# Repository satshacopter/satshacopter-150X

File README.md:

<h1 style="font-family: courier;" align="center">satshacopter 150X</h1>
<p align="center">

<div align="center"><i>An open source,small, low cost and fabbable quad X drone.</i></div>
</p>  

satshacopter 150X
--

satshacopter 150X is a quadcopter built around the **[satshakit mini flight controller](https://github.com/satshakit/satshakit-mini-flight-controller)** and derived from its big brother **[satshacopter 250X](https://github.com/satshacopter/satshacopter-250X)**. It is designed to be **simple and cheap as much as possible**, and to be easily made inside any **Fab Lab**.

150X specifications:

- **150mm mdf frame** and supports
- **open source flight controller**
- **MPU6050 IMU** located exactly at the center
- 4 x 3100kv **brushless motors**
- 4 x 6A **ESCs**
- **MultiWii** compatible
- Hobby King 4 channel **remote and receiver**
- 1000mah 2S 65C **LiPo battery** 
- costs around **100€**

Here you can look about the **MultiWii pin mapping** of the satshakit mini flight controller board:

And here you can che the required components in the **Bill of Material** table:

|name|description|vendor|link|price|notes|
|:---:| :---:|:---:|:---:|:---:|:---:|
|2.4Ghz4Ch TxRx V2|4ch mode 2 remote control and receiver|Hobby King|[link](http://www.hobbyking.com/hobbyking/store/__66499__Hobby_King_2_4Ghz_4Ch_Tx_Rx_V2_Mode_2_EU_Warehouse_.html)|23.14€|-|
|Turnigy Graphene|battery 1000mah 2s 65C|Hobby King|[link](https://hobbyking.com/en_us/graphene-1000mah-2s-65c-w-xt60.html)|8.42€|-|
|LDPOWER D150 Multicopter Power System|4 x MT1306-3100KV motors and 4 x 6A esc|Hobby King EU|[link](https://hobbyking.com/en_us/ldpower-d150-multicopter-power-system-mt1306-3100kv-4-x-4-5-4-pack.html)|59.26€|propellers Included|
|IMU 6DOF|MPU6050 Gyro + Acc IMU|Ebay|[link](http://www.ebay.de/itm/MPU-6050-GY-521-3-Achsen-Gyroskop-Accelerometer-Kreisel-Board-Sensor-Arduino-21-/121887579651)|5.39€|-|
|LiPo Charger and Balancer|800mah 3s LiPo charger|Hobby King|[link](http://www.hobbyking.com/hobbyking/store/uh_viewitem.asp?idproduct=77525)|6.99€|-|
|Fligh Controller|satshakit mini flight controller|various|[link](https://github.com/satshakit/satshakit-flight-controller)|4.00-8.00€|depending on the quantity|
||||**Total price**|103.2€+4/8€|-|

NOTE: prices may change over time on the respective vendors, and also it is highly dependand on the quantity of drones you want to make.

Downloads
--

If you want to build by yourself a satshacopter 150X, please download the detailed **satshacopter 250X build manual** as a reference guide:

- [satshacopter 250X detailed build manual](https://github.com/satshacopter/satshacopter-250X/raw/master/docs/250X/satshacopter-250x-building-manual.pdf)

Following you can find all the **design files** you need to make it:

- [satshakit mini flight controller eagle board](https://github.com/satshacopter/satshacopter-150X/raw/master/eagle_projects/satshakit_mini_flight_controller/satshakit_mini_fc.brd)
- [satshakit mini flight controller eagle sch](https://github.com/satshacopter/satshacopter-150X/raw/master/eagle_projects/satshakit_mini_flight_controller/satshakit_mini_fc.sch)
- [satshakit mini flight controller internal traces png](https://github.com/satshacopter/satshacopter-150X/raw/master/media/satshakit_mini_fc_internal.png)
- [satshakit flight controller cut png](https://github.com/satshacopter/satshacopter-150X/raw/master/media/satshakit_mini_fc_cut.png)
- [mini frame and supports Rhino](https://github.com/satshacopter/satshacopter-150X/raw/master/design_files/frame_and_supports_3mm.3dm)
- [mini frame dxf](https://github.com/satshacopter/satshacopter-150X/raw/master/design_files/frame.dxf)
- [mini supports dxf](https://github.com/satshacopter/satshacopter-150X/raw/master/design_files/supports.dxf)
- [mini foot Rhino](https://github.com/satshacopter/satshacopter-150X/raw/master/design_files/foot.3dm)
- [mini foot STL](https://github.com/satshacopter/satshacopter-150X/raw/master/design_files/foot.stl)

Media
--

Some images of a satshacopter 150X:

Safety
--

Please try always to fly safe.

Here are my personal safety recommendations, especially for experimental drones of which you are not sure on how they can behave:

- make sure to always keep an HUGE distance between you and the drone
- always place yourself on the back of the drone before starting flying
- always have the direct sight to the drone and make sure that its orientation is clear for you (use different colors or LEDs)
- fly in private areas where no public can access
- make sure that nobody can come near the drone while you are flying
- make sure that you cannot destroy anything that you have around you with the drone
- check the wind and the weather before flying, if outdoor
- never go too high (no more than 1/2 meters in these cases)
- do not fly on top of someone (neither yourself)
- first try to fly few cm above the ground to see if everything is correct
- try to avoid using carbon fiber props (they are really like rotating knifes) but use plastic props
- try to use smaller drones with smaller props for really experimental tests
- triple check all the screws and that the frame is not cracked somewhere
- triple check all the DIY electronics, if it fails in-flight can be extremely dangerous
- make sure that the batteries are full charged (both transmitter and the LiPos)

Authors
--

- Daniele Ingrassia

Contact
--

- **ingrassiada@gmail.com**
- **[linkedin](http://it.linkedin.com/in/danieleingrassia)**

Thanks
--

Aldo Sollazzo<br />
[Noumena](http://noumena.io/)<br />
Carrer de Pere IV 29-35, 4-1, Poblenou, 08018, Barcelona, Spain<br />
t: (+34) 652964886<br />
aldo@noumena.io <br />

[Fablab Kamp-Lintfort](http://fablab.hochschule-rhein-waal.de/index.php/de/)<br />
Hochschule Rhein-Waal<br />
Friedrich-Heinrich-Allee 25, 47475 Kamp-Lintfort, Germany<br />
fablab@hochschule-rhein-waal.de

License
--

This work is licensed under the terms of the open source license: Creative Commons Attribution-ShareAlike 4.0 International ([CC BY-SA 4.0](https://creativecommons.org/licenses/by-sa/4.0/)).

Disclaimer  
--

<div class="align-justify">
This hardware/software is provided "as is", and you use the hardware/software at your own risk. Under no circumstances shall any author be liable for direct, indirect, special, incidental, or consequential damages resulting from the use, misuse, or inability to use this hardware/software, even if the authors have been advised of the possibility of such damages.</div>

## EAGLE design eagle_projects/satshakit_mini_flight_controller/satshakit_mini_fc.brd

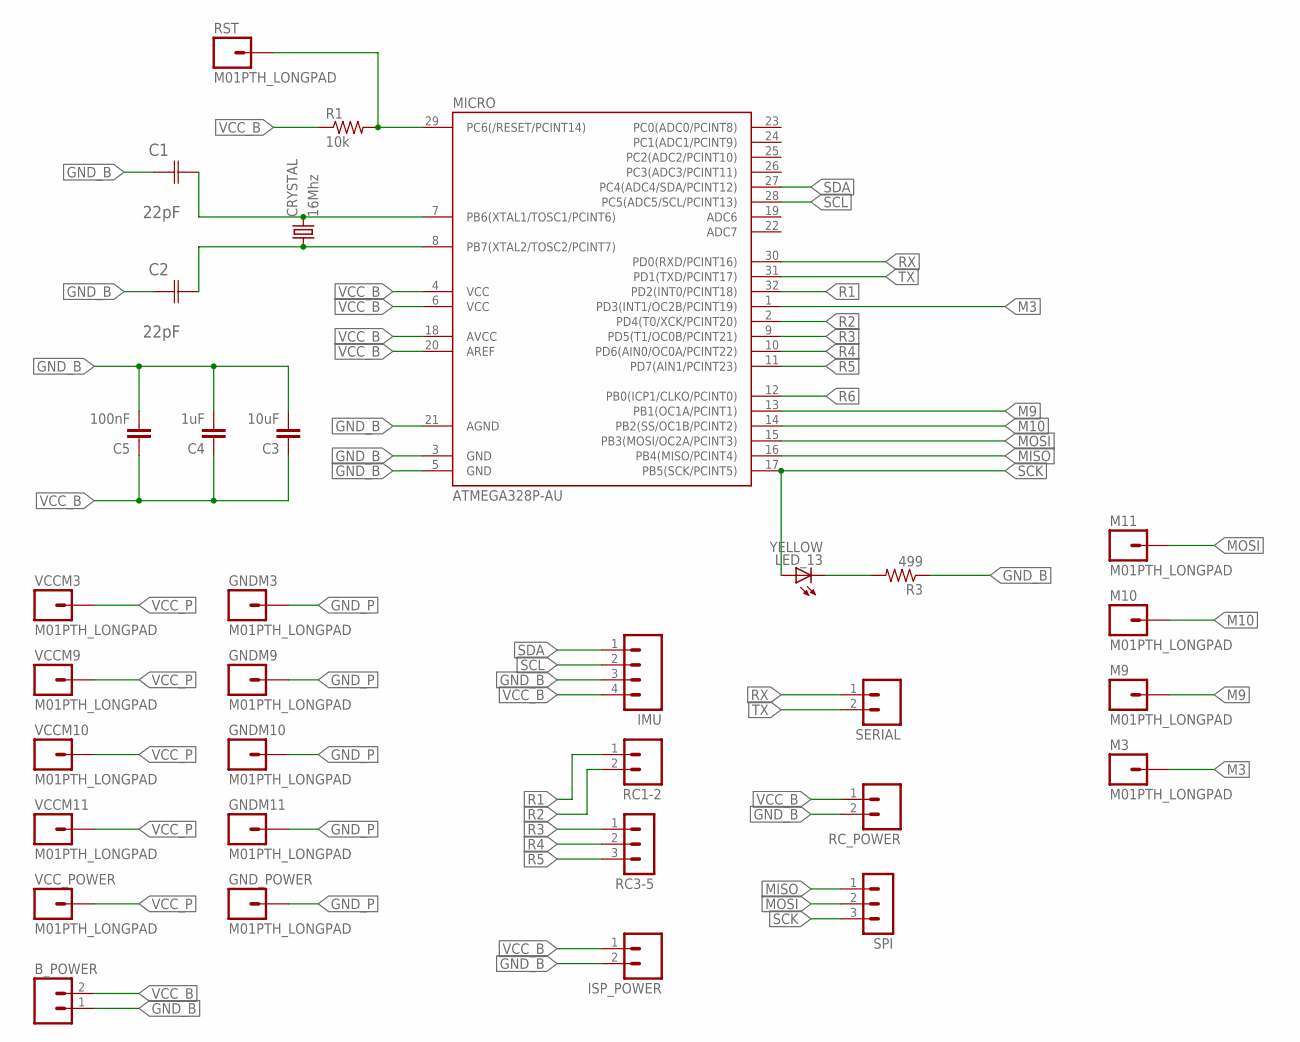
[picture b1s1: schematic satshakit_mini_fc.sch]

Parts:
B_POWER: M02LOCK_LONGPADS; 1X02_LOCK_LONGPADS
C1, C2: 22pF; CAPC3216X178N
C3: 10uF; 1206
C4: 1uF; 1206
C5: 100nF; 1206
CRYSTAL: 16Mhz; CSM-7X-DU
GNDM3, GNDM9, GNDM10, GNDM11: M01PTH_LONGPAD; 1X01_LONGPAD
GND_POWER: M01PTH_LONGPAD; 1X01_LONGPAD
IMU: M04; 04P
ISP_POWER: M02LOCK_LONGPADS; 1X02_LOCK_LONGPADS
LED_13: YELLOW; 1206
M3, M9, M10, M11: M01PTH_LONGPAD; 1X01_LONGPAD
MICRO: ATMEGA328P-AU; TQFP32-08
R1: 10k; 1206
R3: 499; 1206
RC1-2: M02; 02P
RC3-5: MA03-1
RC_POWER: M02LOCK_LONGPADS; 1X02_LOCK_LONGPADS
RST: M01PTH_LONGPAD; 1X01_LONGPAD
SERIAL: M02LOCK_LONGPADS; 1X02_LOCK_LONGPADS
SPI: MA03-1
VCCM3, VCCM9, VCCM10, VCCM11: M01PTH_LONGPAD; 1X01_LONGPAD
VCC_POWER: M01PTH_LONGPAD; 1X01_LONGPAD

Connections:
GND_B: B_POWER.1, C1.1 (C1), C2.1 (C1), C3.2, C4.2, C5.2, IMU.3, ISP_POWER.2, MICRO.3 (GND), MICRO.5 (GND), MICRO.21 (AGND), R3.1, RC_POWER.2
GND_P: GNDM3.1, GNDM9.1, GNDM10.1, GNDM11.1, GND_POWER.1
M3: M3.1, MICRO.1 (PD3(INT1/OC2B/PCINT19))
M9: M9.1, MICRO.13 (PB1(OC1A/PCINT1))
M10: M10.1, MICRO.14 (PB2(SS/OC1B/PCINT2))
MISO: MICRO.16 (PB4(MISO/PCINT4)), SPI.1
MOSI: M11.1, MICRO.15 (PB3(MOSI/OC2A/PCINT3)), SPI.2
unnamed: C1.2 (C2), CRYSTAL.2, MICRO.7 (PB6(XTAL1/TOSC1/PCINT6))
unnamed: MICRO.29 (PC6(/RESET/PCINT14)), R1.2, RST.1
unnamed: C2.2 (C2), CRYSTAL.1, MICRO.8 (PB7(XTAL2/TOSC2/PCINT7))
unnamed: LED_13.2 (C), R3.2
R1: MICRO.32 (PD2(INT0/PCINT18)), RC1-2.1
R2: MICRO.2 (PD4(T0/XCK/PCINT20)), RC1-2.2
R3: MICRO.9 (PD5(T1/OC0B/PCINT21)), RC3-5.1
R4: MICRO.10 (PD6(AIN0/OC0A/PCINT22)), RC3-5.2
R5: MICRO.11 (PD7(AIN1/PCINT23)), RC3-5.3
R6: MICRO.12 (PB0(ICP1/CLKO/PCINT0))
RX: MICRO.30 (PD0(RXD/PCINT16)), SERIAL.1
SCK: LED_13.1 (A), MICRO.17 (PB5(SCK/PCINT5)), SPI.3
SCL: IMU.2, MICRO.28 (PC5(ADC5/SCL/PCINT13))
SDA: IMU.1, MICRO.27 (PC4(ADC4/SDA/PCINT12))
TX: MICRO.31 (PD1(TXD/PCINT17)), SERIAL.2
VCC_B: B_POWER.2, C3.1, C4.1, C5.1, IMU.4, ISP_POWER.1, MICRO.4 (VCC), MICRO.6 (VCC), MICRO.18 (AVCC), MICRO.20 (AREF), R1.1, RC_POWER.1
VCC_P: VCCM3.1, VCCM9.1, VCCM10.1, VCCM11.1, VCC_POWER.1

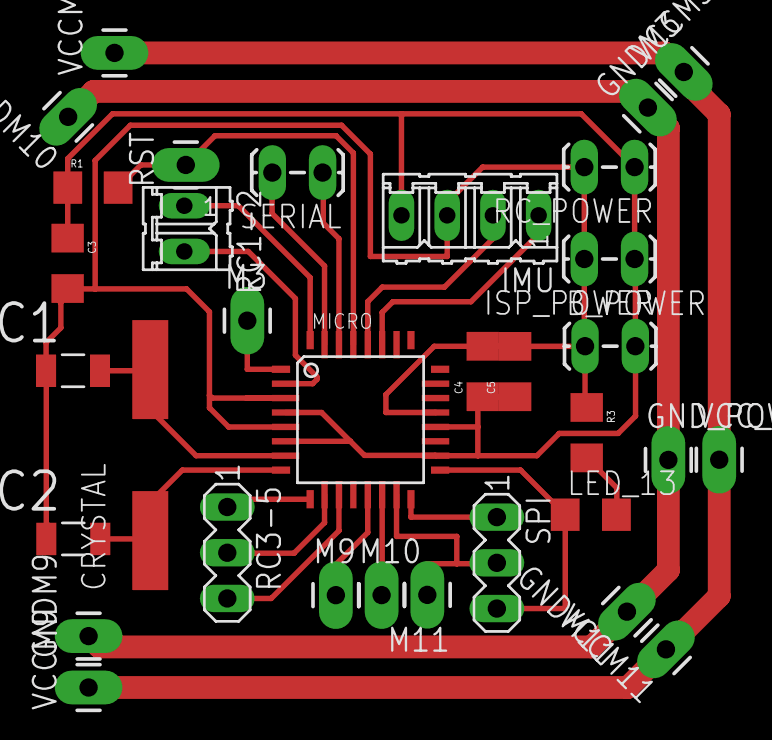
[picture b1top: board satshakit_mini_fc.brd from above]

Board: 2 copper layers, 33 parts (0 on the bottom side), 23 nets.

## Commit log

2017-01-22 added some data
2017-01-22 readme edit
2017-01-22 added design files
2017-01-22 added png of the board
2017-01-22 added download links
2017-01-22 changed readme
2017-01-22 added images
2017-01-22 added bolds
2017-01-25 added thanks
2017-01-26 adjusted the format of the thanks section
2017-06-24 added safety recommendations
2020-05-31 license change

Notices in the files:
parts and their libraries:
01_SparkFun: Licensing: CC v3.0 Share-Alike You are welcome to use this library for commercial purposes.
